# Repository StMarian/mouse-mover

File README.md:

# mouse-mover

A battery-powered dock that keeps a computer awake without installing anything
on it. The mouse sits on top of the dock. Every few minutes a coin vibration
motor under the mouse's optical sensor runs for a second, and the sensor reads
that as movement.

STM32F103C8T6 · C · STM32 HAL · CMake · Unity · KiCad · OpenSCAD

## Features

- Countdown to the next pulse on a 2-digit 7-segment display, `--` while the motor runs
- Period of 2, 4, 9, 14 or 59 minutes, set with a single button
- The setting survives power-off (stored in flash)
- Runs from 2 × AA cells through a 3.3 V boost converter

## Usage

Hold the button for 0.5 s to open the settings. The display blinks and shows
the current period; each short press steps to the next one. After 5 s without
a press the choice is saved and the countdown restarts.

## Hardware

- MCU: STM32F103C8T6
- Power: 2 × AA, MCP1640 boost converter to 3.3 V, power switch
- Display: 2-digit common-cathode 7-segment, multiplexed by the MCU
- Input: one push button, debounced with an RC filter
- Output: coin vibration motor switched by an N-MOSFET, with a flyback diode
- SWD header for programming and debugging

## Repository

| Folder | Contents |
|---|---|
| [`firmware/`](firmware) | STM32CubeMX project, application code, host unit tests |
| [`hardware/`](hardware) | KiCad schematic and PCB |
| [`case/`](case) | 3D-printed case (OpenSCAD) |

## License

See [LICENSE](LICENSE).

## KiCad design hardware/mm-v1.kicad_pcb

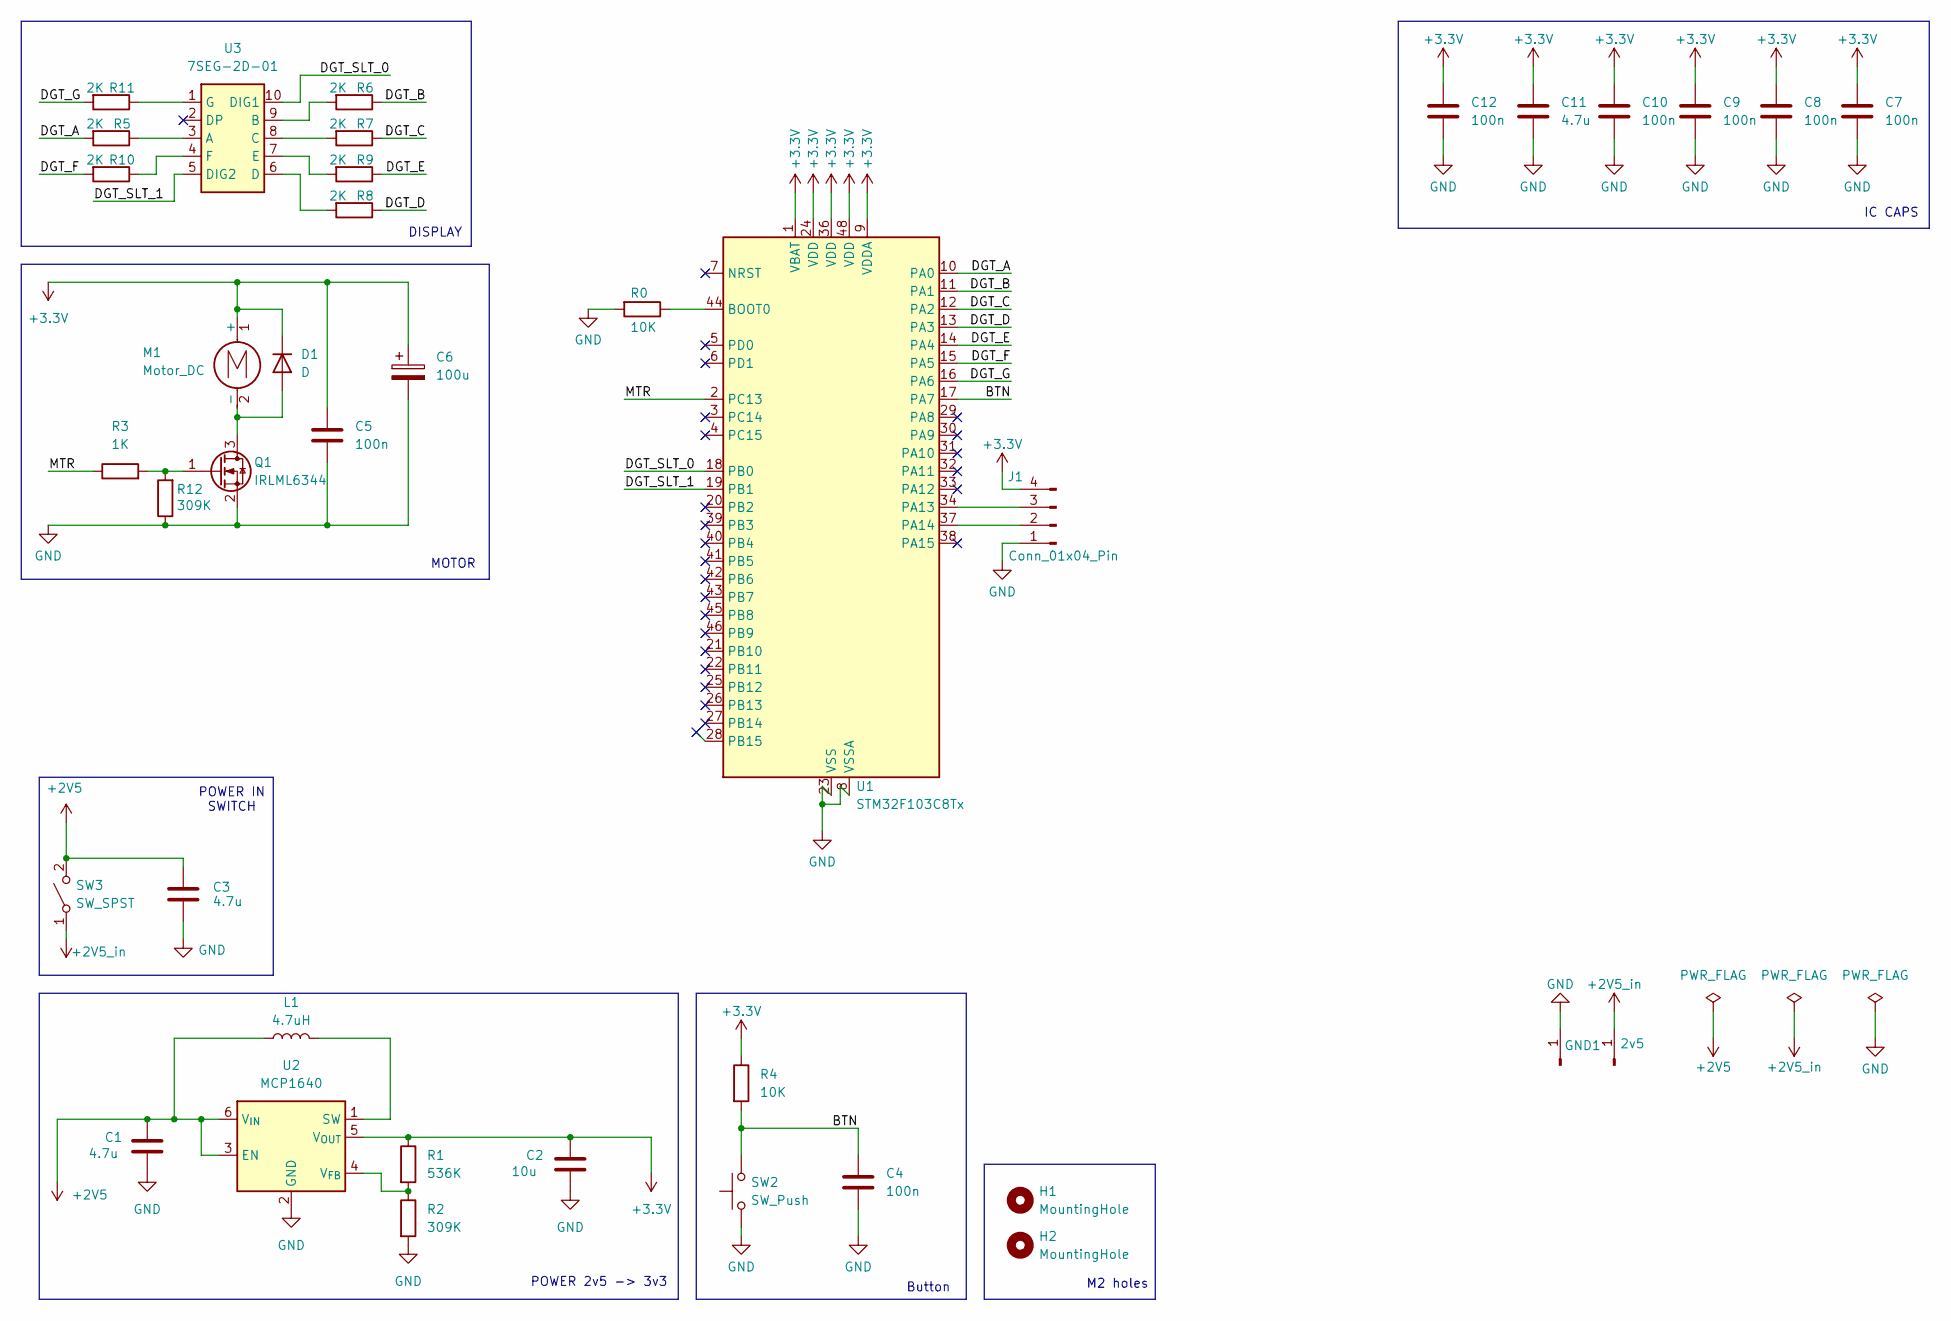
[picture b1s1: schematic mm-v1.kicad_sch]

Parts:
2v5: 2v5; SolderWirePad_1x01_SMD_2x4mm
C1, C3, C11: 4.7u; C_0805_2012Metric
C2: 10u; C_0805_2012Metric
C4, C5, C7, C8, C9, C10, C12: 100n; C_0805_2012Metric
C6: 100u; CP_Elec_6.3x5.7
D1: D; D_SOD-323
GND1: GND; SolderWirePad_1x01_SMD_2x4mm
H1, H2: MountingHole; MountingHole_2.2mm_M2
J1: Conn_01x04_Pin; PinHeader_1x04_P2.54mm_Vertical
L1: 4.7uH; L_Ferrocore_DLG-0504
M1: Motor_DC; JST_GH_BM02B-GHS-TBT_1x02-1MP_P1.25mm_Vertical
Q1: IRLML6344; SOT-23
R0, R4: 10K; R_0805_2012Metric
R1: 536K; R_0805_2012Metric
R2, R12: 309K; R_0805_2012Metric
R3: 1K; R_0805_2012Metric
R5, R6, R7, R8, R9, R10, R11: 2K; R_0805_2012Metric
SW2: SW_Push; JST_GH_BM02B-GHS-TBT_1x02-1MP_P1.25mm_Vertical
SW3: SW_SPST; JST_GH_BM02B-GHS-TBT_1x02-1MP_P1.25mm_Vertical
U1: STM32F103C8Tx; LQFP-48_7x7mm_P0.5mm
U2: MCP1640; SOT-23-6
U3: 7SEG-2D-01; PinHeader_2x05_P2.54mm_Vertical

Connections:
+2V5: C1.1, C3.1, L1.1, SW3.2 (B), U2.3 (EN), U2.6 (V_{IN})
+2V5_in: 2v5.1 (Pin_1_1), SW3.1 (A)
+3.3V: C2.1, C5.1, C6.1, C7.1, C8.1, C9.1, C10.1, C11.1, C12.1, D1.1 (K), J1.4, M1.1 (+), R1.1, R4.1, U1.1 (VBAT), U1.9 (VDDA), U1.24 (VDD), U1.36 (VDD), U1.48 (VDD), U2.5 (V_{OUT})
/BTN: C4.2, R4.2, SW2.2, U1.17 (PA7)
/DGT_A: R5.2, U1.10 (PA0)
/DGT_B: R6.1, U1.11 (PA1)
/DGT_C: R7.1, U1.12 (PA2)
/DGT_D: R8.1, U1.13 (PA3)
/DGT_E: R9.1, U1.14 (PA4)
/DGT_F: R10.2, U1.15 (PA5)
/DGT_G: R11.2, U1.16 (PA6)
/DGT_SLT_0: U1.18 (PB0), U3.10 (DIG1)
/DGT_SLT_1: U1.19 (PB1), U3.5 (DIG2)
/MTR: R3.1, U1.2 (PC13)
GND: C1.2, C2.2, C3.2, C4.1, C5.2, C6.2, C7.2, C8.2, C9.2, C10.2, C11.2, C12.2, GND1.1 (Pin_1_1), J1.1, Q1.2 (S), R0.2, R2.2, R12.1, SW2.1, U1.8 (VSSA), U1.23 (VSS), U1.35 (VSS), U1.47 (VSS), U2.2 (GND)
unnamed: D1.2 (A), M1.2 (-), Q1.3 (D)
unnamed: J1.2, U1.37 (PA14)
unnamed: J1.3, U1.34 (PA13)
unnamed: Q1.1 (G), R3.2, R12.2
unnamed: R0.1, U1.44 (BOOT0)
unnamed: L1.2, U2.1 (SW)
unnamed: R1.2, R2.1, U2.4 (V_{FB})
unnamed: R5.1, U3.3 (A)
unnamed: R6.2, U3.9 (B)
unnamed: R7.2, U3.8 (C)
unnamed: R8.2, U3.6 (D)
unnamed: R9.2, U3.7 (E)
unnamed: R10.1, U3.4 (F)
unnamed: R11.1, U3.1 (G)

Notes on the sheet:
Button
POWER 2v5 -> 3v3
M2 holes
MOTOR
POWER IN SWITCH
DISPLAY
IC CAPS

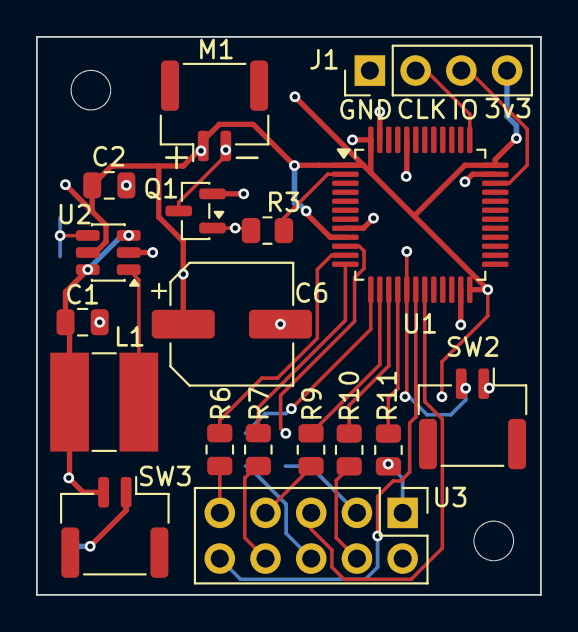
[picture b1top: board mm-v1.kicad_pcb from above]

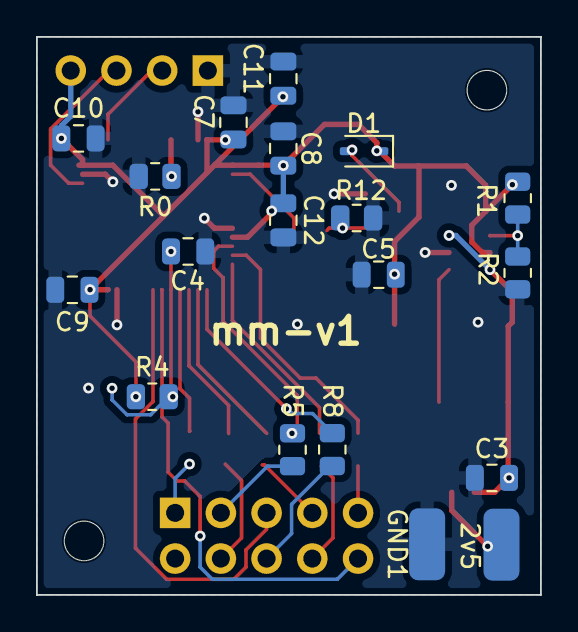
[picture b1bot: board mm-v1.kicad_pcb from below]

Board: 2 copper layers, 28.0 x 31.0 mm, 39 parts (19 on the bottom side), 29 nets.

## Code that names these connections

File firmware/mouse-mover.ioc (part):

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Mcu.Name=STM32F103C(8-B)Tx
Mcu.Package=LQFP48
Mcu.UserName=STM32F103C8Tx
PA0-WKUP.GPIOParameters=GPIO_Label
PA0-WKUP.GPIO_Label=DGT_A
PA0-WKUP.Signal=GPIO_Output
PA1.GPIOParameters=GPIO_Label
PA1.GPIO_Label=DGT_B
PA1.Signal=GPIO_Output
PA13.Mode=Serial_Wire
PA13.Signal=SYS_JTMS-SWDIO
PA14.Mode=Serial_Wire
PA14.Signal=SYS_JTCK-SWCLK
PA2.GPIOParameters=GPIO_Label
PA2.GPIO_Label=DGT_C
PA2.Signal=GPIO_Output
PA3.GPIOParameters=GPIO_Label
PA3.GPIO_Label=DGT_D
PA3.Signal=GPIO_Output
PA4.GPIOParameters=GPIO_Label
PA4.GPIO_Label=DGT_E
PA4.Signal=GPIO_Output
PA5.GPIOParameters=GPIO_Label
PA5.GPIO_Label=DGT_F
PA5.Signal=GPIO_Output
PA6.GPIOParameters=GPIO_Label
PA6.GPIO_Label=DGT_G
PA6.Signal=GPIO_Output
PA7.GPIOParameters=GPIO_PuPd,GPIO_Label
PA7.GPIO_Label=BTN
PA7.GPIO_PuPd=GPIO_PULLUP
PA7.Signal=GPIO_Input
PB0.GPIOParameters=GPIO_Label
PB0.GPIO_Label=DGT_SLT_0
PB0.Signal=GPIO_Output
PB1.GPIOParameters=GPIO_Label
PB1.GPIO_Label=DGT_SLT_1
PB1.Signal=GPIO_Output
PC13-TAMPER-RTC.GPIOParameters=GPIO_Label
PC13-TAMPER-RTC.GPIO_Label=LED
PC13-TAMPER-RTC.Signal=GPIO_Output
board=custom
